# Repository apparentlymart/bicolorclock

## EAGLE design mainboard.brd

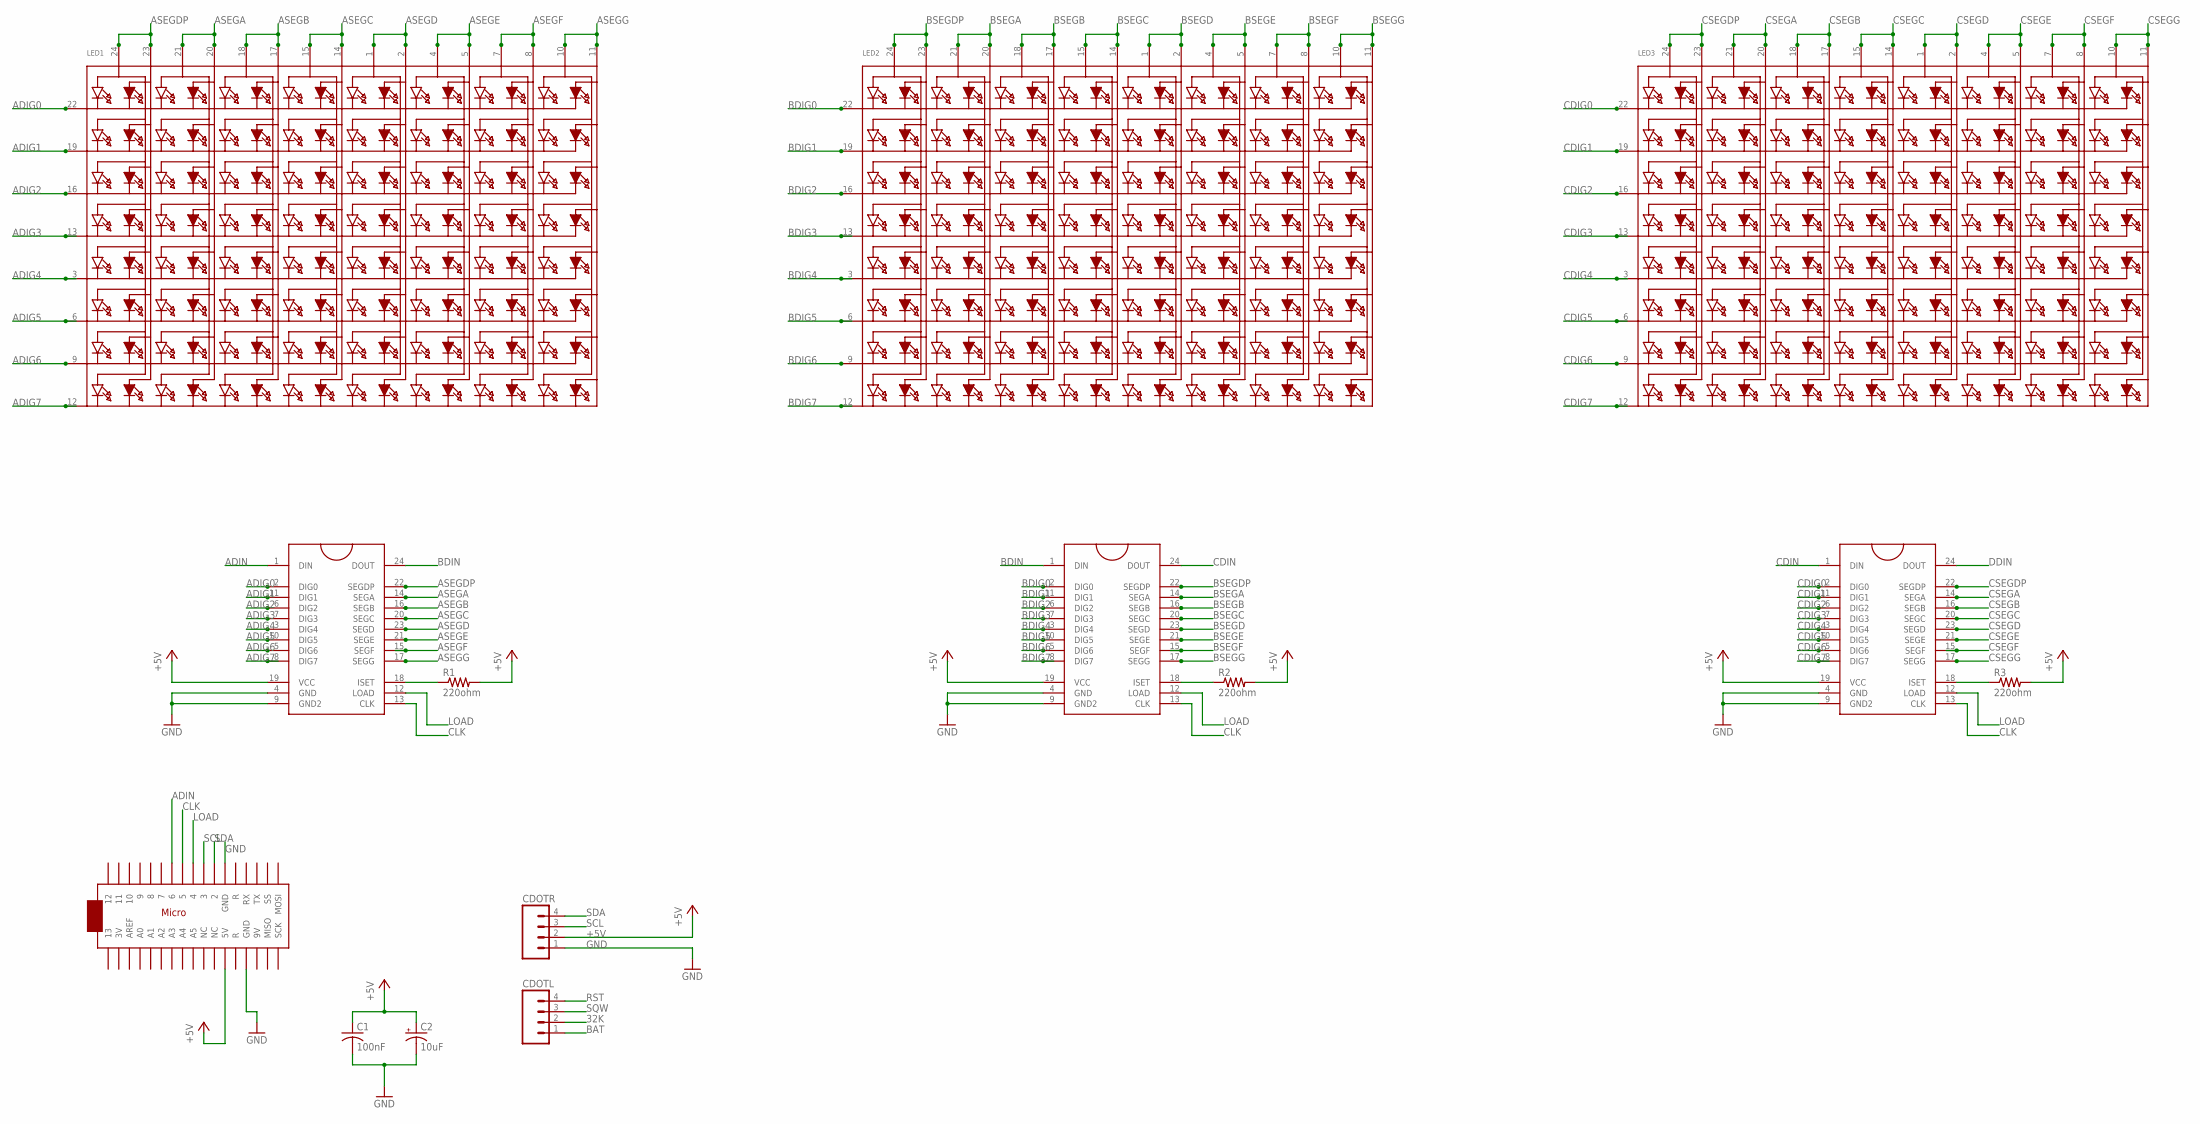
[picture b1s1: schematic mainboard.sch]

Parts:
ARDUINO: ARDUINOMICRO
C1: 100nF; C050-030X075
C2: 10uF; E2,5-6
CDOTL: M04PTH; 1X04
CDOTR: M04PTH; 1X04
LED1, LED2, LED3: SEGMENT_8X8_BICOLOR_ROWCATHODEMI2A883XX; SEGMENT_BICOL_BL-M12A883XX
MAX1, MAX2, MAX3: MAX7219DIP; DIL24
R1, R2, R3: 220ohm; 0207/10

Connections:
32K: CDOTL.2
+5V: ARDUINO.P$23 (5V), C1.1, C2.+, CDOTR.2, MAX1.19 (VCC), MAX2.19 (VCC), MAX3.19 (VCC), R1.2, R2.2, R3.2
ADIG0: LED1.22 (K1), MAX1.2 (DIG0)
ADIG1: LED1.19 (K2), MAX1.11 (DIG1)
ADIG2: LED1.16 (K3), MAX1.6 (DIG2)
ADIG3: LED1.13 (K4), MAX1.7 (DIG3)
ADIG4: LED1.3 (K5), MAX1.3 (DIG4)
ADIG5: LED1.6 (K6), MAX1.10 (DIG5)
ADIG6: LED1.9 (K7), MAX1.5 (DIG6)
ADIG7: LED1.12 (K8), MAX1.8 (DIG7)
ADIN: ARDUINO.P$7 (6), MAX1.1 (DIN)
ASEGA: LED1.20 (A4), LED1.21 (A3), MAX1.14 (SEGA)
ASEGB: LED1.17 (A6), LED1.18 (A5), MAX1.16 (SEGB)
ASEGC: LED1.14 (A8), LED1.15 (A7), MAX1.20 (SEGC)
ASEGD: LED1.1 (A9), LED1.2 (A10), MAX1.23 (SEGD)
ASEGDP: LED1.23 (A2), LED1.24 (A1), MAX1.22 (SEGDP)
ASEGE: LED1.4 (A11), LED1.5 (A12), MAX1.21 (SEGE)
ASEGF: LED1.7 (A13), LED1.8 (A14), MAX1.15 (SEGF)
ASEGG: LED1.10 (A15), LED1.11 (A16), MAX1.17 (SEGG)
BAT: CDOTL.1
BDIG0: LED2.22 (K1), MAX2.2 (DIG0)
BDIG1: LED2.19 (K2), MAX2.11 (DIG1)
BDIG2: LED2.16 (K3), MAX2.6 (DIG2)
BDIG3: LED2.13 (K4), MAX2.7 (DIG3)
BDIG4: LED2.3 (K5), MAX2.3 (DIG4)
BDIG5: LED2.6 (K6), MAX2.10 (DIG5)
BDIG6: LED2.9 (K7), MAX2.5 (DIG6)
BDIG7: LED2.12 (K8), MAX2.8 (DIG7)
BDIN: MAX1.24 (DOUT), MAX2.1 (DIN)
BSEGA: LED2.20 (A4), LED2.21 (A3), MAX2.14 (SEGA)
BSEGB: LED2.17 (A6), LED2.18 (A5), MAX2.16 (SEGB)
BSEGC: LED2.14 (A8), LED2.15 (A7), MAX2.20 (SEGC)
BSEGD: LED2.1 (A9), LED2.2 (A10), MAX2.23 (SEGD)
BSEGDP: LED2.23 (A2), LED2.24 (A1), MAX2.22 (SEGDP)
BSEGE: LED2.4 (A11), LED2.5 (A12), MAX2.21 (SEGE)
BSEGF: LED2.7 (A13), LED2.8 (A14), MAX2.15 (SEGF)
BSEGG: LED2.10 (A15), LED2.11 (A16), MAX2.17 (SEGG)
CDIG0: LED3.22 (K1), MAX3.2 (DIG0)
CDIG1: LED3.19 (K2), MAX3.11 (DIG1)
CDIG2: LED3.16 (K3), MAX3.6 (DIG2)
CDIG3: LED3.13 (K4), MAX3.7 (DIG3)
CDIG4: LED3.3 (K5), MAX3.3 (DIG4)
CDIG5: LED3.6 (K6), MAX3.10 (DIG5)
CDIG6: LED3.9 (K7), MAX3.5 (DIG6)
CDIG7: LED3.12 (K8), MAX3.8 (DIG7)
CDIN: MAX2.24 (DOUT), MAX3.1 (DIN)
CLK: ARDUINO.P$8 (5), MAX1.13 (CLK), MAX2.13 (CLK), MAX3.13 (CLK)
CSEGA: LED3.20 (A4), LED3.21 (A3), MAX3.14 (SEGA)
CSEGB: LED3.17 (A6), LED3.18 (A5), MAX3.16 (SEGB)
CSEGC: LED3.14 (A8), LED3.15 (A7), MAX3.20 (SEGC)
CSEGD: LED3.1 (A9), LED3.2 (A10), MAX3.23 (SEGD)
CSEGDP: LED3.23 (A2), LED3.24 (A1), MAX3.22 (SEGDP)
CSEGE: LED3.4 (A11), LED3.5 (A12), MAX3.21 (SEGE)
CSEGF: LED3.7 (A13), LED3.8 (A14), MAX3.15 (SEGF)
CSEGG: LED3.10 (A15), LED3.11 (A16), MAX3.17 (SEGG)
DDIN: MAX3.24 (DOUT)
GND: ARDUINO.P$12 (GND), ARDUINO.P$21 (GND), C1.2, C2.-, CDOTR.1, MAX1.4 (GND), MAX1.9 (GND2), MAX2.4 (GND), MAX2.9 (GND2), MAX3.4 (GND), MAX3.9 (GND2)
LOAD: ARDUINO.P$9 (4), MAX1.12 (LOAD), MAX2.12 (LOAD), MAX3.12 (LOAD)
unnamed: MAX1.18 (ISET), R1.1
unnamed: MAX2.18 (ISET), R2.1
unnamed: MAX3.18 (ISET), R3.1
RST: CDOTL.4
SCL: ARDUINO.P$10 (3), CDOTR.3
SDA: ARDUINO.P$11 (2), CDOTR.4
SQW: CDOTL.3

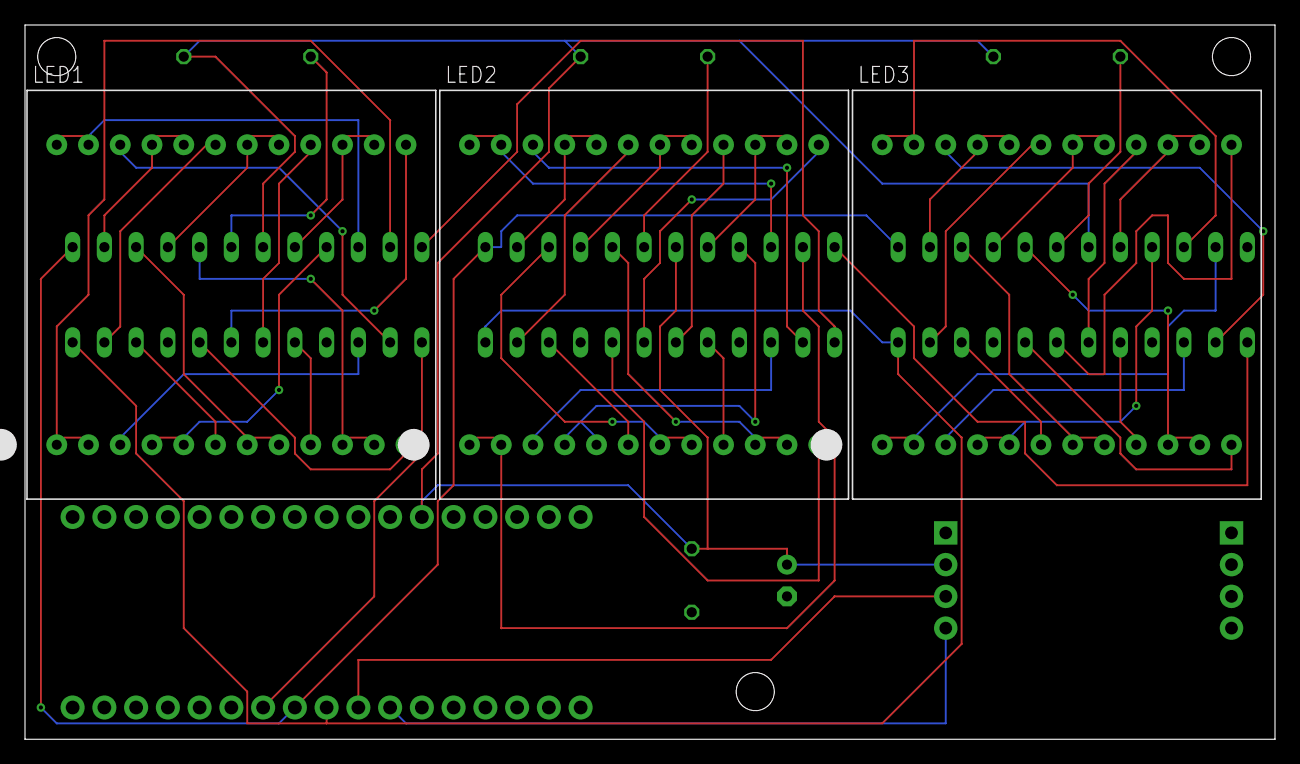
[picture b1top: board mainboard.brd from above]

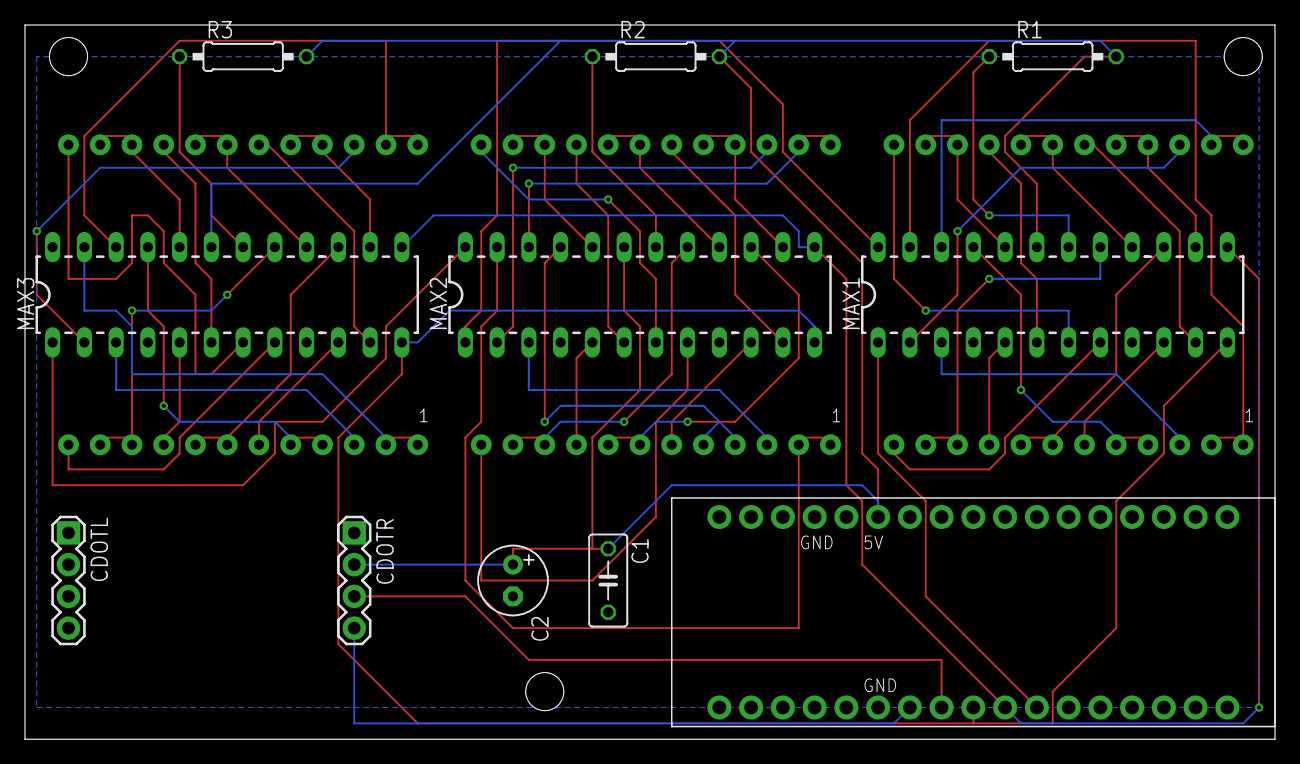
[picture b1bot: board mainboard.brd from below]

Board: 2 copper layers, 100.0 x 57.1 mm, 14 parts (11 on the bottom side), 60 nets.

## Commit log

2013-10-13 Import of first version

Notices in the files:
parts and their libraries:
SparkFun-DigitalIC: Licensing: CC v3.0 Share-Alike You are welcome to use this library for commercial purposes.
